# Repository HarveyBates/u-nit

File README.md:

An STM32 based general purpose board designed for mixed signal applications. 

### Features:

- Wide input voltage (4.5 - 40 VDC)
- Palm size (65 mm x 80 mm)
- Replaceable fuse (10 A) and reverse-polarity protection
- Line regulation and outputs (VIN, 5V, 3V3)
- CAN transceiver built in with 120 ohm termination
- Debug through ST-Link (2 connector varieties)
- 4 high-power, high-side switches (2 A per channel or 6 A if chained)
- General purpose interfaces (2 USART, 2 ADC, 2 DAC, 1 I2C, >1 GPI)
- Piezo buzzer for audible feedback

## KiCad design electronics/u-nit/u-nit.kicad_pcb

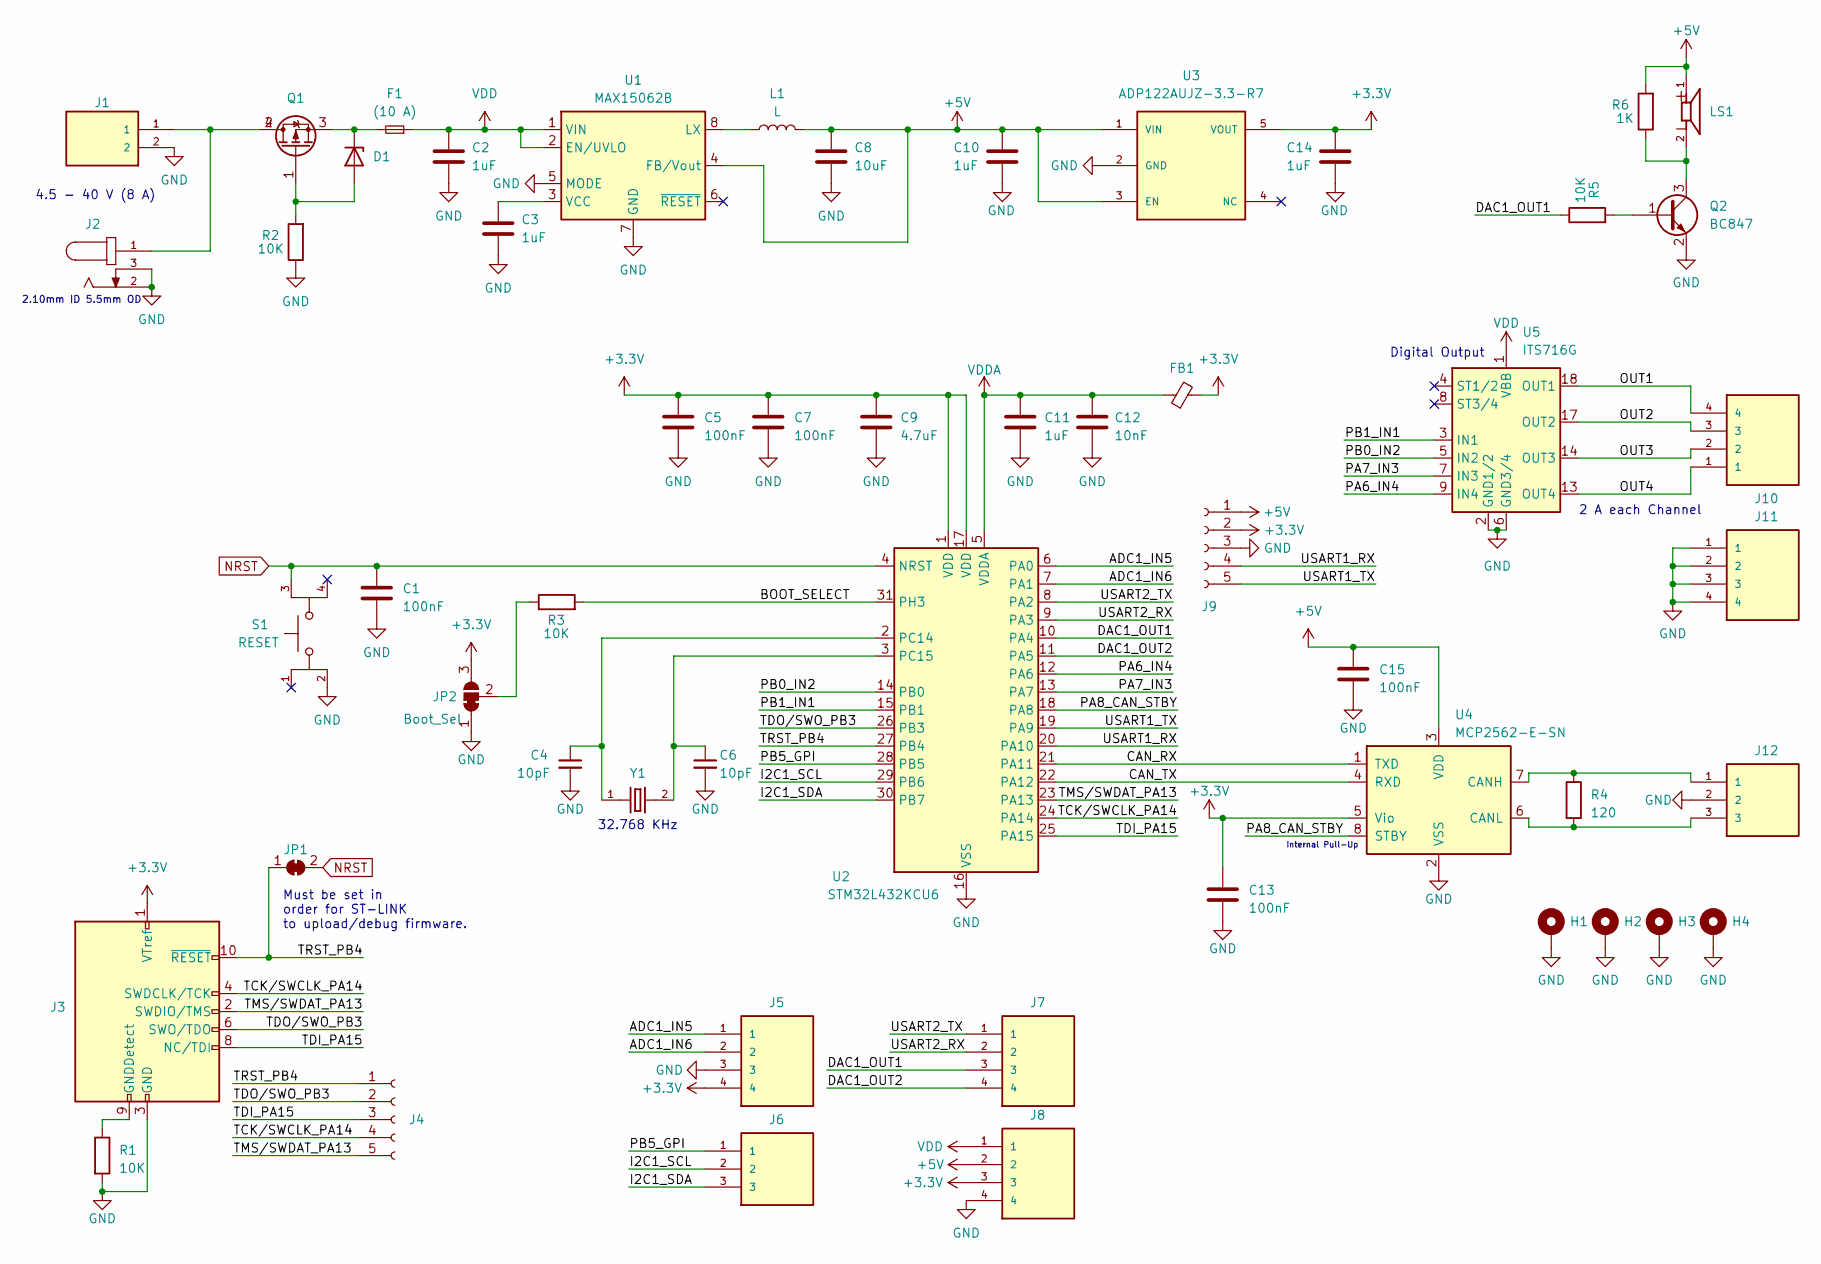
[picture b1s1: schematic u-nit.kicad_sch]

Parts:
C1, C5, C7, C13, C15: 100nF; C_0805_2012Metric
C2, C3, C10, C11, C14: 1uF; C_0805_2012Metric
C4, C6: 10pF; C_0805_2012Metric
C8: 10uF; C_0805_2012Metric
C9: 4.7uF; C_0805_2012Metric
C12: 10nF; C_0805_2012Metric
D1: D_Zener; MMSZ4700T1G
F1: (10 A); 0154010.DRL; Part 0154010.DRL
FB1: R_0805_2012Metric; Part 2508051027Y1
H1, H2, H3, H4: MountingHole_Pad; MountingHole_3.2mm_M3_Pad_TopBottom
J1: TBP02R2-381-02BE
J2: PJ-002A
J3: Conn_ARM_JTAG_SWD_10; PinHeader_2x05_P1.27mm_Vertical; Part GRPB052VWVN-RC
J4, J9: Conn_01x05_Socket; PinSocket_1x05_P2.54mm_Vertical
J5, J7, J8, J10, J11: TBP02R2-381-04BE
J6, J12: TBP02R2-381-03BE
JP1: SolderJumper-2_P1.3mm_Bridged_Pad1.0x1.5mm
JP2: Boot_Sel; SolderJumper-3_P1.3mm_Bridged12_Pad1.0x1.5mm_NumberLabels
L1: L; VLS6045EX-470M; Part VLS6045EX-470M
LS1: PKMCS0909E4000-R1; PARTREV May 22, 2020
Q1: DMP6023LE-13
Q2: BC847; SOT-23
R1, R2, R3, R5: 10K; R_0805_2012Metric
R4: 120; R_0805_2012Metric
R6: 1K; R_0805_2012Metric
S1: RESET; TL3301AF160QG; PARTREV E; DigiKey_Part_Number EG2526TR-ND
U1: MAX15062B; DFN-8_2x2mm_P0.5mm
U2: STM32L432KCU6; QFN-32-1EP_5x5mm_P0.5mm_EP3.45x3.45mm
U3: ADP122AUJZ-3.3-R7
U4: MCP2562-E-SN; SOIC-8_3.9x4.9mm_P1.27mm
U5: ITS716G; SOIC-20W_7.5x12.8mm_P1.27mm
Y1: ECS-.327-12.5-34R-C-TR; PARTREV 2016

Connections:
+3.3V: C5.1, C7.1, C9.1, C13.1, C14.1, FB1.2, J3.1 (VTref), J5.4, J8.3, J9.2, JP2.3 (B), U2.1 (VDD), U2.17 (VDD), U3.5 (VOUT), U4.5 (Vio)
+5V: C8.1, C10.1, C15.1, J8.2, J9.1, L1.2, LS1.1, R6.2, U1.4 (FB/Vout), U3.1 (VIN), U3.3 (EN), U4.3 (VDD)
/ADC1_IN5: J5.1, U2.6 (PA0)
/ADC1_IN6: J5.2, U2.7 (PA1)
/BOOT_SELECT: R3.2, U2.31 (PH3)
/CAN_RX: U2.21 (PA11), U4.1 (TXD)
/CAN_TX: U2.22 (PA12), U4.4 (RXD)
/DAC1_OUT1: J7.3, R5.1, U2.10 (PA4)
/DAC1_OUT2: J7.4, U2.11 (PA5)
/I2C1_SCL: J6.2, U2.29 (PB6)
/I2C1_SDA: J6.3, U2.30 (PB7)
/OUT1: J10.4, U5.18 (OUT1)
/OUT2: J10.3, U5.17 (OUT2)
/OUT3: J10.2, U5.14 (OUT3)
/OUT4: J10.1, U5.13 (OUT4)
/PA6_IN4: U2.12 (PA6), U5.9 (IN4)
/PA7_IN3: U2.13 (PA7), U5.7 (IN3)
/PA8_CAN_STBY: U2.18 (PA8), U4.8 (STBY)
/PB0_IN2: U2.14 (PB0), U5.5 (IN2)
/PB1_IN1: U2.15 (PB1), U5.3 (IN1)
/PB5_GPI: J6.1, U2.28 (PB5)
/TCK/SWCLK_PA14: J3.4 (SWDCLK/TCK), J4.4, U2.24 (PA14)
/TDI_PA15: J3.8 (NC/TDI), J4.3, U2.25 (PA15)
/TDO/SWO_PB3: J3.6 (SWO/TDO), J4.2, U2.26 (PB3)
/TMS/SWDAT_PA13: J3.2 (SWDIO/TMS), J4.5, U2.23 (PA13)
/TRST_PB4: J3.10 (~RESET), J4.1, JP1.1 (A), U2.27 (PB4)
/USART1_RX: J9.4, U2.20 (PA10)
/USART1_TX: J9.5, U2.19 (PA9)
/USART2_RX: J7.2, U2.9 (PA3)
/USART2_TX: J7.1, U2.8 (PA2)
GND: C1.2, C2.2, C3.2, C4.2, C5.2, C6.2, C7.2, C8.2, C9.2, C10.2, C11.2, C12.2, C13.2, C14.2, C15.2, H1.1, H2.1, H3.1, H4.1, J1.2, J2.2, J2.3, J3.3 (GND), J3.5 (GND), J5.3, J8.4, J9.3, J11.1, J11.2, J11.3, J11.4, J12.2, JP2.1 (A), Q2.2 (E), R1.2, R2.1, S1.2, U1.5 (MODE), U1.7 (GND), U2.16 (VSS), U2.32 (VSS), U2.33 (VSS), U3.2 (GND), U4.2 (VSS), U5.2 (GND1/2), U5.6 (GND3/4)
NRST: C1.1, JP1.2 (B), S1.3, U2.4 (NRST)
unnamed: D1.2 (A), Q1.1, R2.2
unnamed: D1.1 (K), F1.2, Q1.3
unnamed: J1.1, J2.1, Q1.2, Q1.4
unnamed: J3.9 (GNDDetect), R1.1
unnamed: JP2.2 (C), R3.1
unnamed: Q2.1 (B), R5.2
unnamed: LS1.2, Q2.3 (C), R6.1
unnamed: L1.1, U1.8 (LX)
unnamed: C3.1, U1.3 (VCC)
unnamed: C4.1, U2.2 (PC14), Y1.1
unnamed: C6.1, U2.3 (PC15), Y1.2
unnamed: J12.1, R4.1, U4.7 (CANH)
unnamed: J12.3, R4.2, U4.6 (CANL)
VDD: C2.1, F1.1, J8.1, U1.1 (VIN), U1.2 (EN/UVLO), U5.1 (VBB), U5.10 (VBB), U5.11 (VBB), U5.12 (VBB), U5.15 (VBB), U5.16 (VBB), U5.19 (VBB), U5.20 (VBB)
VDDA: C11.1, C12.1, FB1.1, U2.5 (VDDA)

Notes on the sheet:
Internal Pull-Up
Digital Output
2 A each Channel
32.768 KHz
2.10mm ID 5.5mm OD
Must be set in order for ST-LINK to upload/debug firmware.
4.5 - 40 V (8 A)

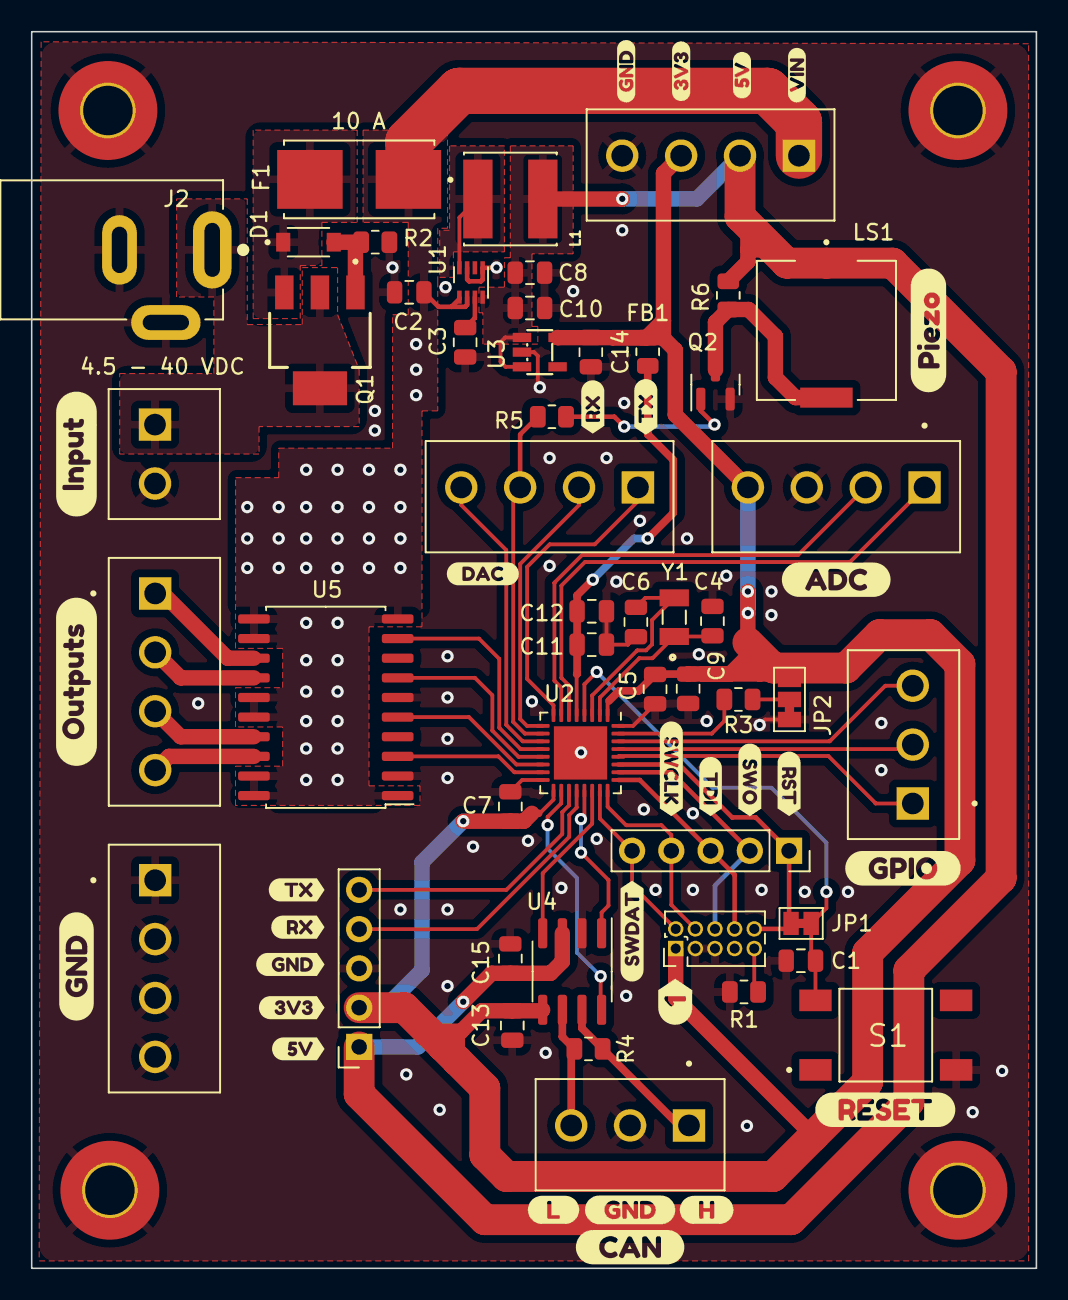
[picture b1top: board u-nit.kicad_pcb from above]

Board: 2 copper layers, 65.0 x 80.0 mm, 82 parts (0 on the bottom side), 47 nets.

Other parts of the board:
kibuzzard-64E9E9CD: G***; kibuzzard-64E9E9CD
kibuzzard-64E9E96D: G***; kibuzzard-64E9E96D
kibuzzard-64E9E97D: G***; kibuzzard-64E9E97D
kibuzzard-64E9E988: G***; kibuzzard-64E9E988
kibuzzard-64E9E995: G***; kibuzzard-64E9E995
kibuzzard-64E9EA0B: G***; kibuzzard-64E9EA0B
kibuzzard-64E9EA19: G***; kibuzzard-64E9EA19
kibuzzard-64E9EAB8: G***; kibuzzard-64E9EAB8
kibuzzard-64E9EAC2: G***; kibuzzard-64E9EAC2
kibuzzard-64E9EAE9: G***; kibuzzard-64E9EAE9
kibuzzard-64E9EAF9: G***; kibuzzard-64E9EAF9
kibuzzard-64E9EB1A: G***; kibuzzard-64E9EB1A
kibuzzard-64E9EB3C: G***; kibuzzard-64E9EB3C
kibuzzard-64E9EB5A: G***; kibuzzard-64E9EB5A
kibuzzard-64E9EB76: G***; kibuzzard-64E9EB76
kibuzzard-64E9EBA4: G***; kibuzzard-64E9EBA4
kibuzzard-64E9EBD0: G***; kibuzzard-64E9EBD0
kibuzzard-64E9EBDF: G***; kibuzzard-64E9EBDF
kibuzzard-64E9EBEF: G***; kibuzzard-64E9EBEF
kibuzzard-64E9EC0B: G***; kibuzzard-64E9EC0B
kibuzzard-64E9EC1A: G***; kibuzzard-64E9EC1A
kibuzzard-64E9EC2C: G***; kibuzzard-64E9EC2C
kibuzzard-64E9EC3B: G***; kibuzzard-64E9EC3B
kibuzzard-64E9EC5C: G***; kibuzzard-64E9EC5C
kibuzzard-64E9EC20: G***; kibuzzard-64E9EC20
kibuzzard-64E9EC55: G***; kibuzzard-64E9EC55
kibuzzard-64E9EC76: G***; kibuzzard-64E9EC76
kibuzzard-64E9EC92: G***; kibuzzard-64E9EC92
kibuzzard-64E9ECC2: G***; kibuzzard-64E9ECC2

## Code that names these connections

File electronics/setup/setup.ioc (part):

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Mcu.Name=STM32L432K(B-C)Ux
Mcu.Package=UFQFPN32
Mcu.UserName=STM32L432KCUx
PA0.Signal=ADCx_IN5
PA1.Signal=ADCx_IN6
PA10.Mode=Asynchronous
PA10.Signal=USART1_RX
PA11.Mode=CAN_Activate
PA11.Signal=CAN1_RX
PA12.Mode=CAN_Activate
PA12.Signal=CAN1_TX
PA13\ (JTMS-SWDIO).Mode=JTAG_5_pins
PA13\ (JTMS-SWDIO).Signal=SYS_JTMS-SWDIO
PA14\ (JTCK-SWCLK).Mode=JTAG_5_pins
PA14\ (JTCK-SWCLK).Signal=SYS_JTCK-SWCLK
PA15\ (JTDI).Mode=JTAG_5_pins
PA15\ (JTDI).Signal=SYS_JTDI
PA2.Mode=Asynchronous
PA2.Signal=USART2_TX
PA3.Mode=Asynchronous
PA3.Signal=USART2_RX
PA4.Signal=COMP_DAC11_group
PA5.Signal=COMP_DAC12_group
PA6.Signal=GPIO_Output
PA7.Signal=GPIO_Output
PA8.Signal=GPIO_Output
PA9.Mode=Asynchronous
PA9.Signal=USART1_TX
PB0.Signal=GPIO_Output
PB1.Signal=GPIO_Output
PB3\ (JTDO-TRACESWO).Mode=JTAG_5_pins
PB3\ (JTDO-TRACESWO).Signal=SYS_JTDO-SWO
PB4\ (NJTRST).Mode=JTAG_5_pins
PB4\ (NJTRST).Signal=SYS_JTRST
PB5.Signal=GPIO_Input
PB6.Mode=I2C
PB6.Signal=I2C1_SCL
PB7.Mode=I2C
PB7.Signal=I2C1_SDA
PC14-OSC32_IN\ (PC14).Mode=LSE-External-Oscillator
PC14-OSC32_IN\ (PC14).Signal=RCC_OSC32_IN
PC15-OSC32_OUT\ (PC15).Mode=LSE-External-Oscillator
PC15-OSC32_OUT\ (PC15).Signal=RCC_OSC32_OUT
RCC.HSE_VALUE=8000000
board=custom

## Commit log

2023-08-26 added 3D img
2023-08-27 exported PCB step and created base container
2023-08-27 added digikey BOM, schematic (pdf) and gerber files
2023-08-27 added bom and img
2023-08-27 more work on 3d-printed enclosure and PCB lid
2023-09-14 added gerber for lid and finalised gerber for both lid and PCB
